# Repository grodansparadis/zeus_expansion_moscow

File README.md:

<h1>Zeus Expansion Moscow</h1>

ESP8266 based wifi add on card with Zeus expansion connector. Fits the 
<a href="http://www.grodansparadis.com/odessa/odessa.html">Odessa</a> module
among other modules.

<hr>

This project is part of the <a href="http://www.vscp.org">VSCP (Very Simple Control Protocol) project</a>. 

<hr>

This project is licensed under the 
<a href="http://creativecommons.org/licenses/by-nc-sa/3.0/">Creative Commons open source license Attribution-NonCommercial-ShareAlike 3.0 Unported</a>. 
Other license options are available by conacting <a href="malto:info@grodansparadis.com">Paradis of the Frog AB</a>

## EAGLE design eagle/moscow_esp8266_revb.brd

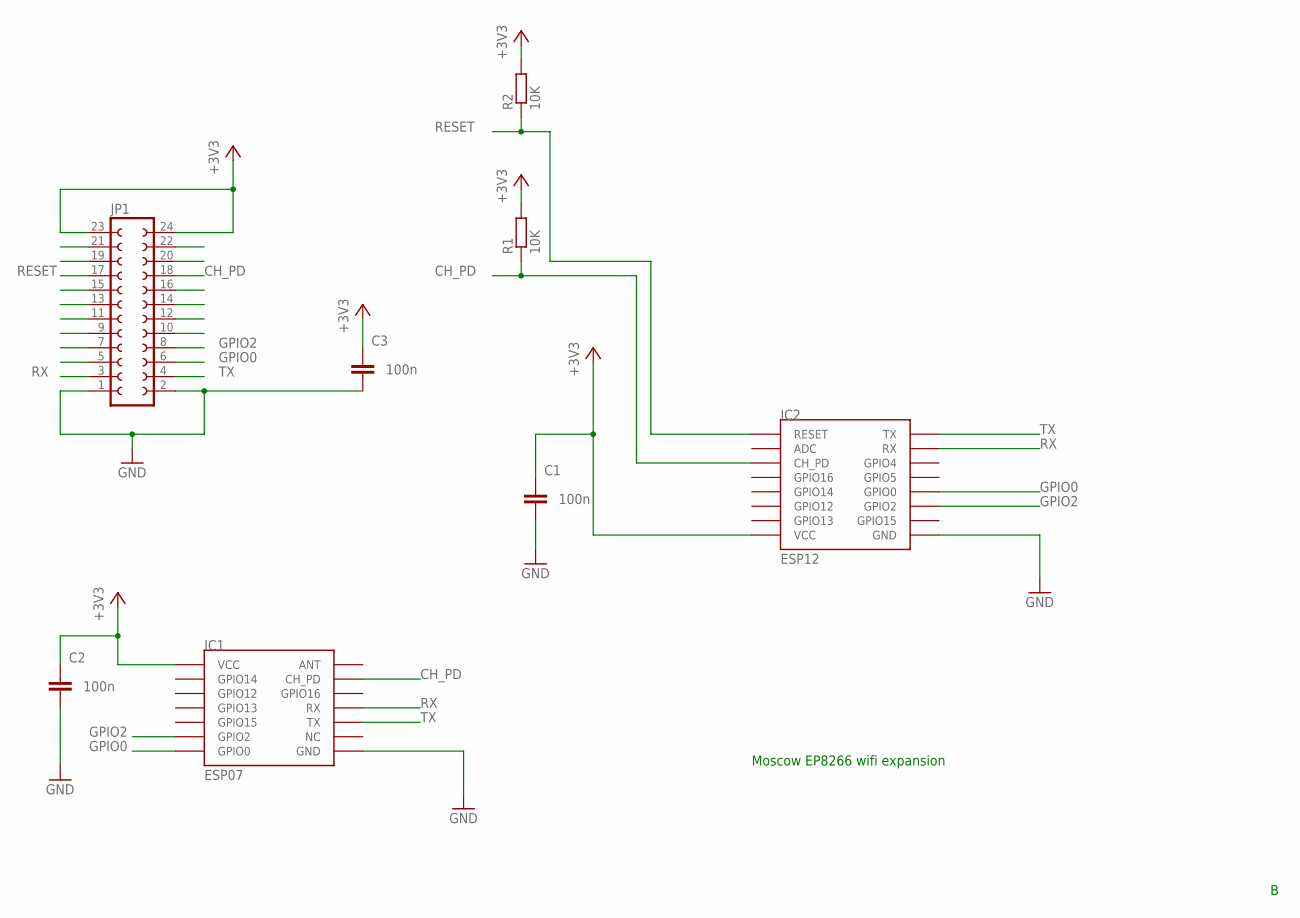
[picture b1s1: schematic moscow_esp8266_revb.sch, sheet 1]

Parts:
C1, C2, C3: 100n; C0805
IC1: ESP07
IC2: ESP12
JP1: FE12-2
R1, R2: 10K; R0805

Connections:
+3V3: C1.1, C2.1, C3.1, IC1.VCC, IC2.VCC, JP1.23, JP1.24, R1.2, R2.2
CH_PD: IC1.CH_PD, IC2.CH_PD, JP1.18, R1.1
GND: C1.2, C2.2, C3.2, IC1.GND, IC2.GND, JP1.1, JP1.2
GPIO0: IC1.GPIO0, IC2.GPIO0, JP1.6
GPIO2: IC1.GPIO2, IC2.GPIO2, JP1.8
RESET: IC2.RESET, JP1.17, R2.1
RX: IC1.RX, IC2.RX, JP1.3
TX: IC1.TX, IC2.TX, JP1.4

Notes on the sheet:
Moscow EP8266 wifi expansion

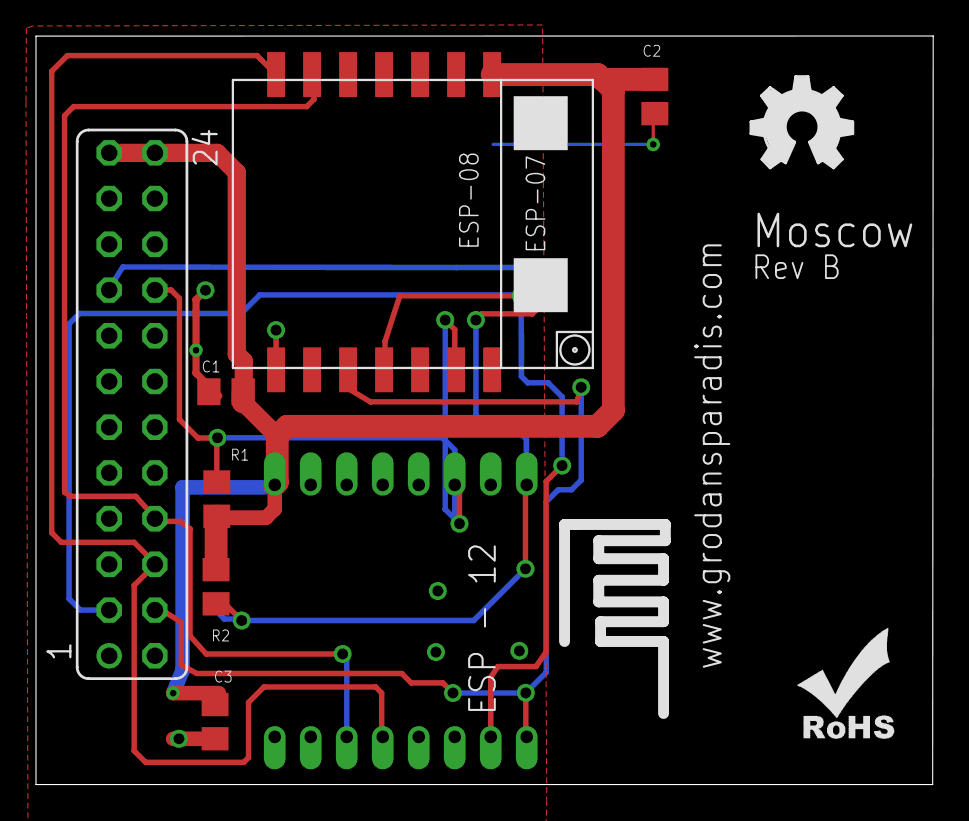
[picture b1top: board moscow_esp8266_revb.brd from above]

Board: 2 copper layers, 49.8 x 41.6 mm, 10 parts (0 on the bottom side), 8 nets.

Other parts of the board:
U$1: OSHW_FILLX200_NOTEXT
U$2: ROHS_SILK

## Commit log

2015-11-03 Making design open
2015-12-17 Updated license and readme
2015-12-22 Enlarged component marking sizes
2015-12-22 Added ground polygon to top layer
